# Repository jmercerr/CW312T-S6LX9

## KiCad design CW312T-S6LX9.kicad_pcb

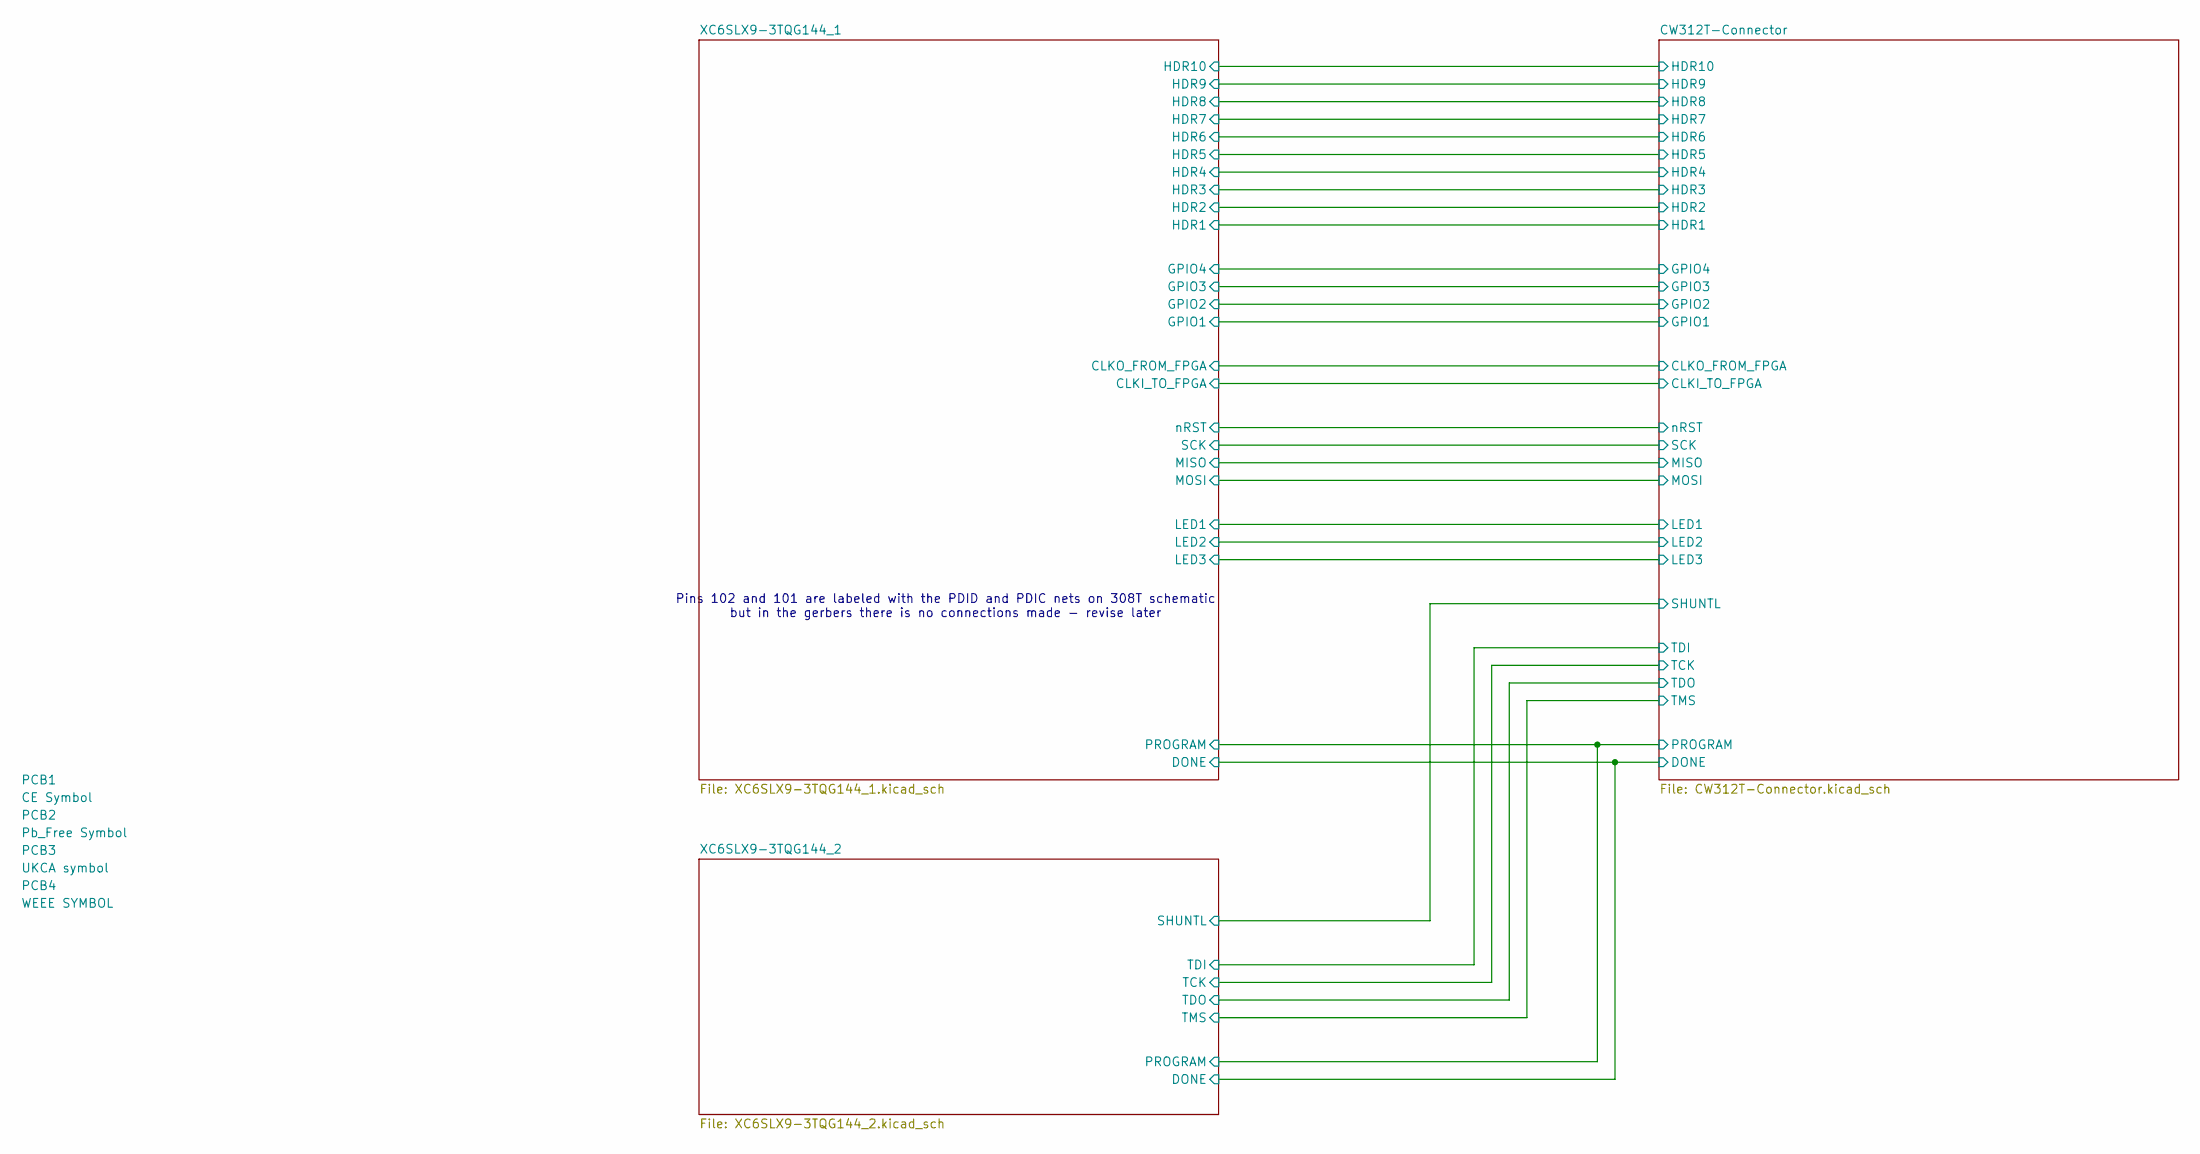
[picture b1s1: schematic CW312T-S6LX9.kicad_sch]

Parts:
PCB1: CE Symbol; CE-Logo_8.5x6mm_SilkScreen
PCB2: Pb_Free Symbol; Pb_Free_8.0x8.0mm_SilkScreen
PCB3: UKCA symbol; UKCA-Logo_8x8mm_SilkScreen
PCB4: WEEE SYMBOL; WEEE-Logo_5.6x8mm_SilkScreen

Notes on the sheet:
Pins 102 and 101 are labeled with the PDID and PDIC nets on 308T schematic but in the gerbers there is no connections made - revise later

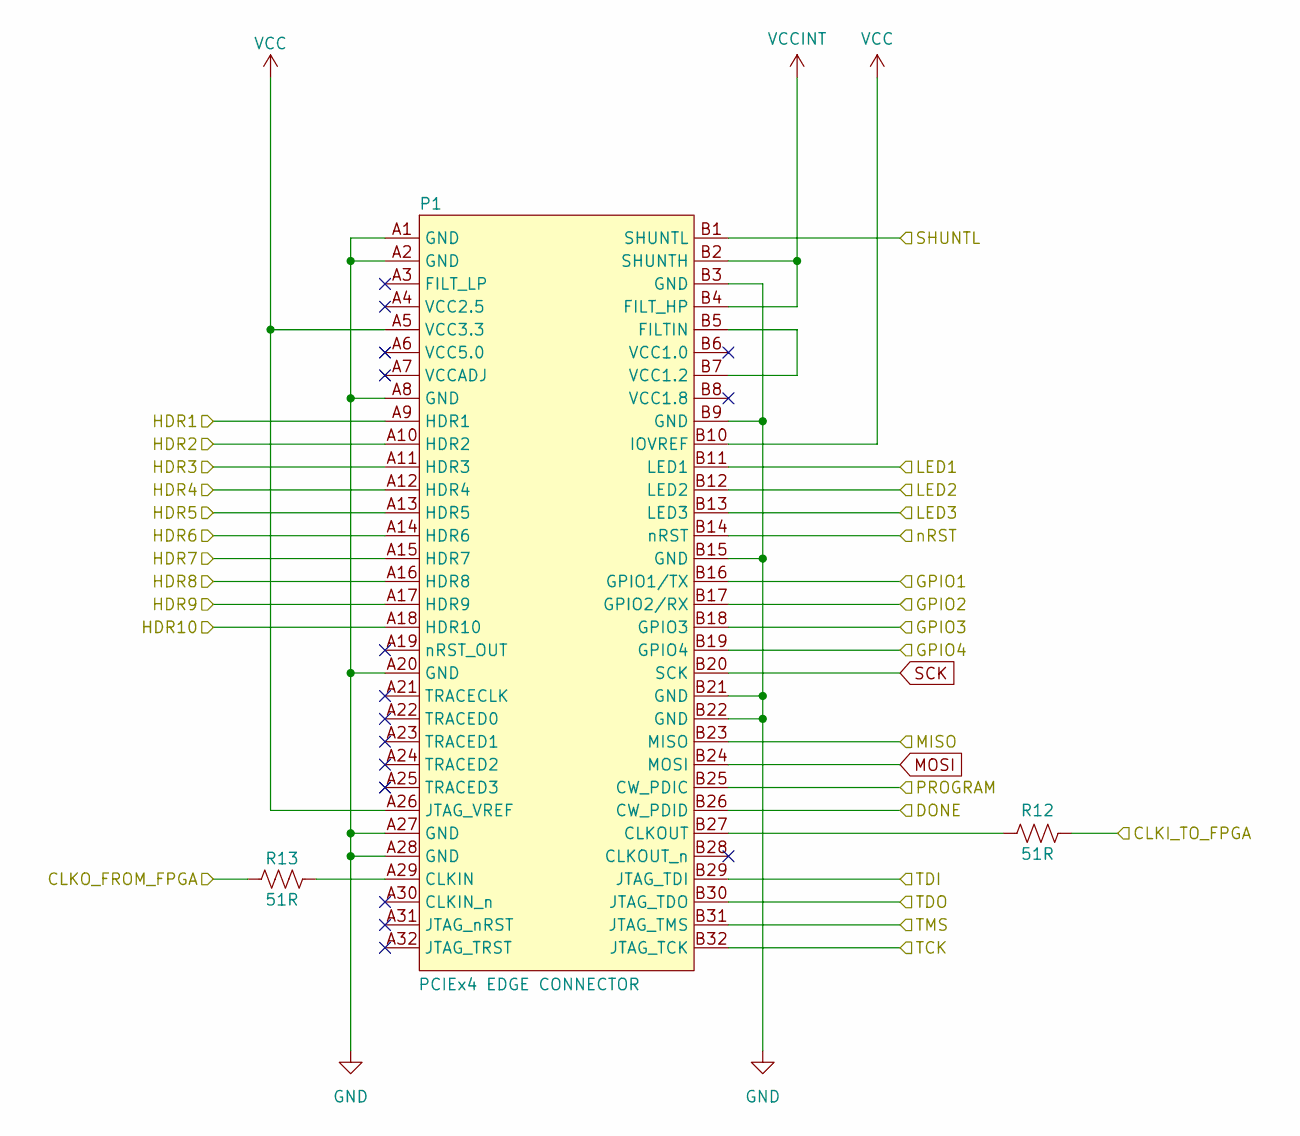
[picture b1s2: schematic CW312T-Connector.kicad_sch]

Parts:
P1: PCIEx4 EDGE CONNECTOR; CW312_Template
R12, R13: RES_51R_0603; R_0603_1608Metric; Manufacturer Part Number RC0603FR-0751RL

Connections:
/CW312T-Connector/CLKI_TO_FPGA: R12.2; also elsewhere on the board
/CW312T-Connector/CLKO_FROM_FPGA: R13.1; also elsewhere on the board
/CW312T-Connector/DONE: P1.B26 (CW_PDID); also elsewhere on the board
/CW312T-Connector/GPIO1: P1.B16 (GPIO1/TX); also elsewhere on the board
/CW312T-Connector/GPIO2: P1.B17 (GPIO2/RX); also elsewhere on the board
/CW312T-Connector/GPIO3: P1.B18 (GPIO3); also elsewhere on the board
/CW312T-Connector/GPIO4: P1.B19 (GPIO4); also elsewhere on the board
/CW312T-Connector/HDR1: P1.A9 (HDR1); also elsewhere on the board
/CW312T-Connector/HDR2: P1.A10 (HDR2); also elsewhere on the board
/CW312T-Connector/HDR3: P1.A11 (HDR3); also elsewhere on the board
/CW312T-Connector/HDR4: P1.A12 (HDR4); also elsewhere on the board
/CW312T-Connector/HDR5: P1.A13 (HDR5); also elsewhere on the board
/CW312T-Connector/HDR6: P1.A14 (HDR6); also elsewhere on the board
/CW312T-Connector/HDR7: P1.A15 (HDR7); also elsewhere on the board
/CW312T-Connector/HDR8: P1.A16 (HDR8); also elsewhere on the board
/CW312T-Connector/HDR9: P1.A17 (HDR9); also elsewhere on the board
/CW312T-Connector/HDR10: P1.A18 (HDR10); also elsewhere on the board
/CW312T-Connector/LED1: P1.B11 (LED1); also elsewhere on the board
/CW312T-Connector/LED2: P1.B12 (LED2); also elsewhere on the board
/CW312T-Connector/LED3: P1.B13 (LED3); also elsewhere on the board
/CW312T-Connector/MISO: P1.B23 (MISO); also elsewhere on the board
/CW312T-Connector/PROGRAM: P1.B25 (CW_PDIC); also elsewhere on the board
/CW312T-Connector/SHUNTL: P1.B1 (SHUNTL); also elsewhere on the board
/CW312T-Connector/TCK: P1.B32 (JTAG_TCK); also elsewhere on the board
/CW312T-Connector/TDI: P1.B29 (JTAG_TDI); also elsewhere on the board
/CW312T-Connector/TDO: P1.B30 (JTAG_TDO); also elsewhere on the board
/CW312T-Connector/TMS: P1.B31 (JTAG_TMS); also elsewhere on the board
/CW312T-Connector/nRST: P1.B14 (nRST); also elsewhere on the board
GND: P1.A1 (GND), P1.A2 (GND), P1.A8 (GND), P1.A20 (GND), P1.A27 (GND), P1.A28 (GND), P1.B3 (GND), P1.B9 (GND), P1.B15 (GND), P1.B21 (GND), P1.B22 (GND); also elsewhere on the board
MOSI: P1.B24 (MOSI); also elsewhere on the board
unnamed: P1.A29 (CLKIN), R13.2
unnamed: P1.B27 (CLKOUT), R12.1
unnamed: P1.B5 (FILTIN), P1.B7 (VCC1.2)
SCK: P1.B20 (SCK); also elsewhere on the board
VCC: P1.A5 (VCC3.3), P1.A26 (JTAG_VREF), P1.B10 (IOVREF); also elsewhere on the board
VCCINT: P1.B2 (SHUNTH), P1.B4 (FILT_HP); also elsewhere on the board

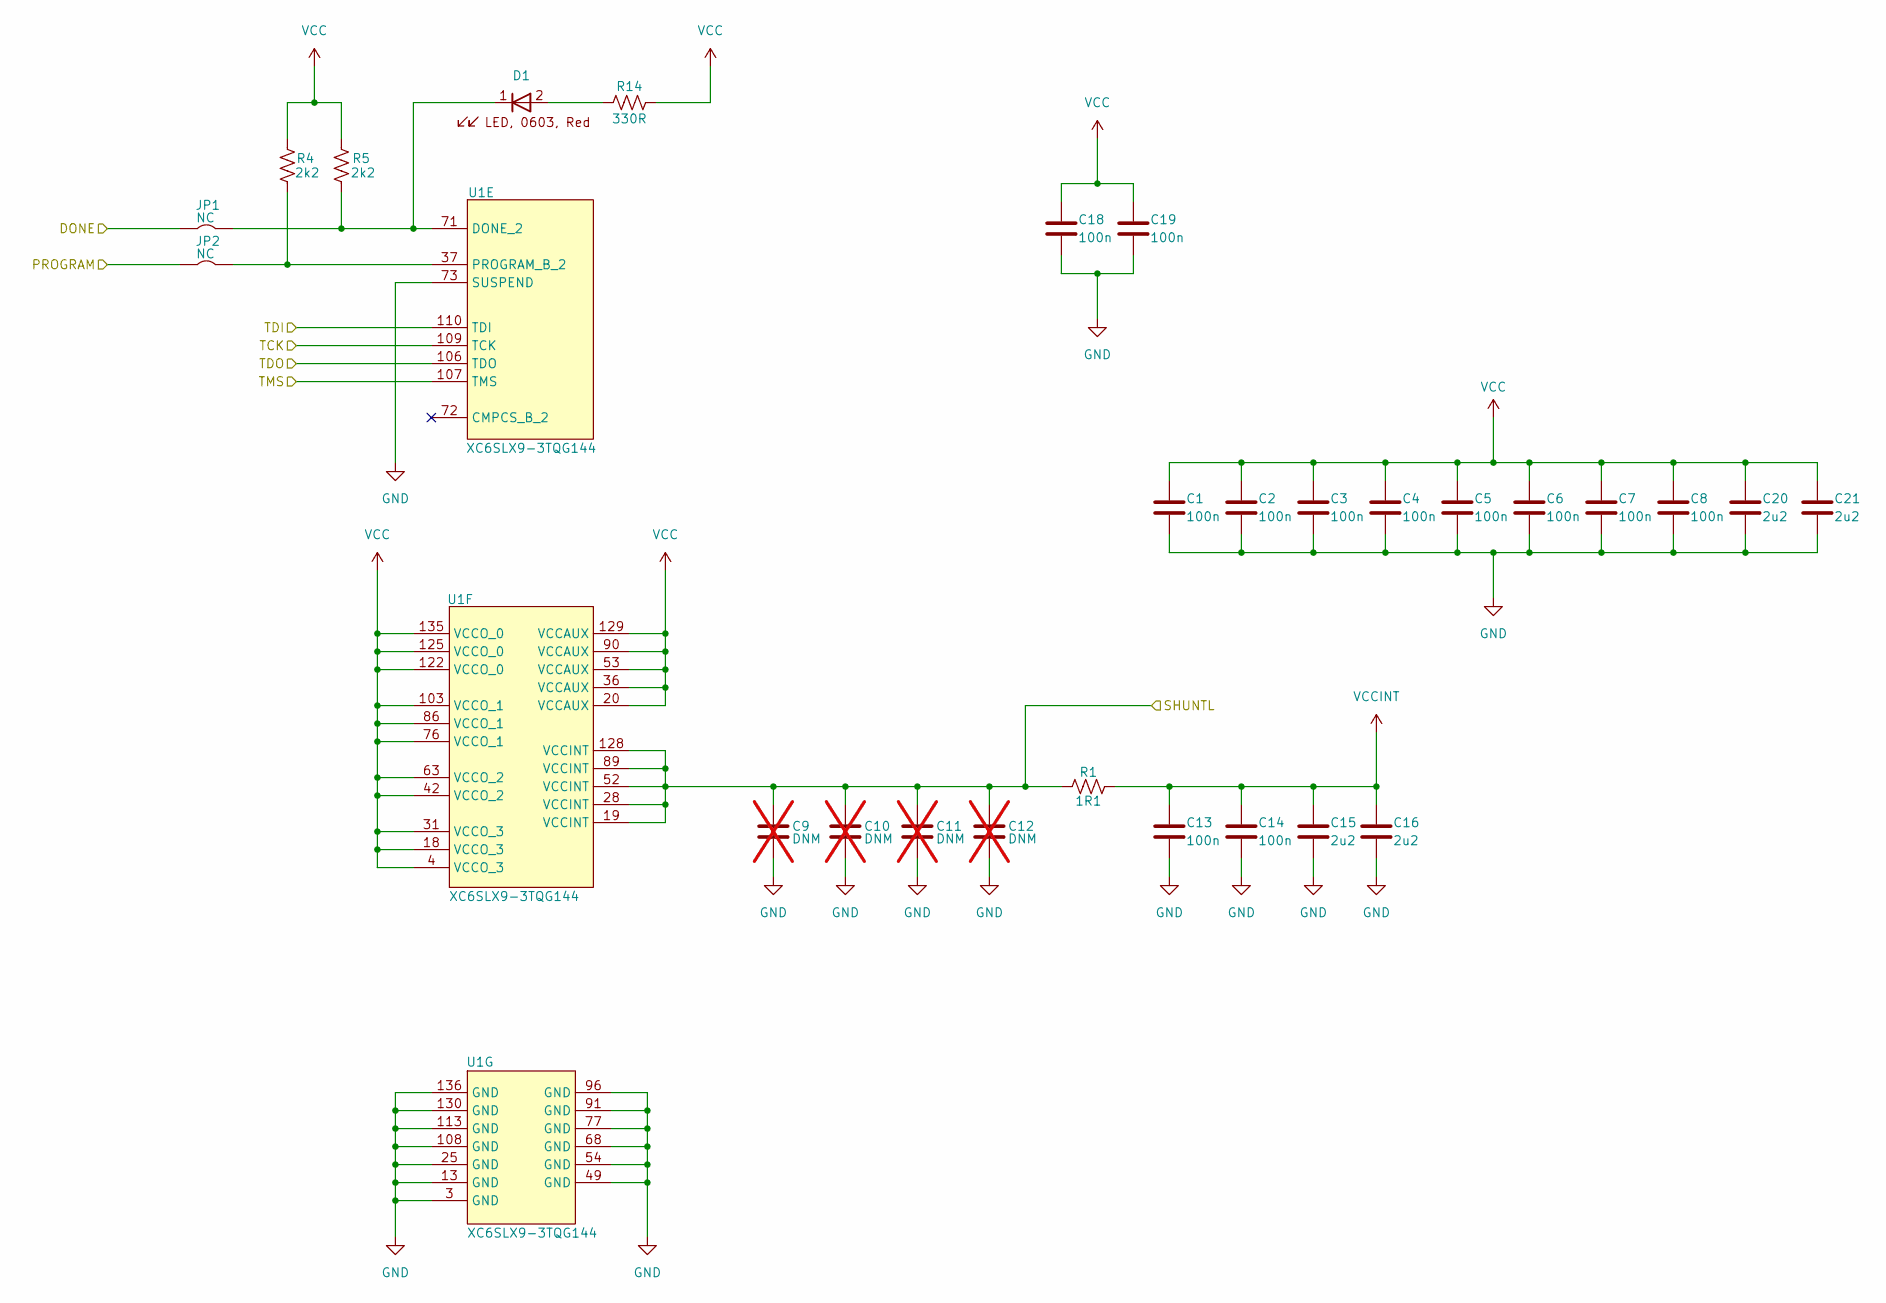
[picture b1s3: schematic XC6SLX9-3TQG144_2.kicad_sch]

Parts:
C1, C2, C3, C4, C5, C6, C7, C8, C13, C14, C18, C19: CAP_100n_6.3V_0603; C_0603_1608Metric; Manufacturer Part Number CC0603KRX7R5BB104
C9, C10, C11, C12: DNM_CAP_0603; C_0603_1608Metric; Manufacturer Part Number C0603C225K4PAC7867; not fitted
C15, C16, C20, C21: CAP_2u2_6.3V_0603; C_0603_1608Metric; Manufacturer Part Number CC0603KRX7R5BB225
D1: APT1608SRCPRV; LED_0603_1608Metric; Manufacturer Part Number APT1608SRCPRV
JP1, JP2: SolderJumper-2_P1.3mm_Bridged2Bar_Pad1.0x1.5mm
R1: RES_1R1_0603; R_0603_1608Metric; Manufacturer Part Number RC0603FR-101R1L
R4, R5: RES_2k2_0603; R_0603_1608Metric; Manufacturer Part Number RC0603FR-072K2L
R14: RES_330R_0603; R_0603_1608Metric; Manufacturer Part Number RC0603FR-07330RL
U1: XC6SLX9-3TQG144; TQFP-144_20x20mm_P0.5mm; Manufacturer Part Number XC6SLX9-3TQG144CXC6SLX9-3TQG144C

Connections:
/CW312T-Connector/DONE: JP1.1; also elsewhere on the board
/CW312T-Connector/PROGRAM: JP2.1; also elsewhere on the board
/CW312T-Connector/SHUNTL: C9.2, C10.2, C11.2, C12.2, R1.1, U1.19 (VCCINT), U1.28 (VCCINT), U1.52 (VCCINT), U1.89 (VCCINT), U1.128 (VCCINT); also elsewhere on the board
/CW312T-Connector/TCK: U1.109 (TCK); also elsewhere on the board
/CW312T-Connector/TDI: U1.110 (TDI); also elsewhere on the board
/CW312T-Connector/TDO: U1.106 (TDO); also elsewhere on the board
/CW312T-Connector/TMS: U1.107 (TMS); also elsewhere on the board
GND: C1.2, C2.2, C3.2, C4.2, C5.2, C6.2, C7.2, C8.2, C9.1, C10.1, C11.1, C12.1, C13.2, C14.2, C15.2, C16.2, C18.2, C19.2, C20.2, C21.2, U1.3 (GND), U1.13 (GND), U1.25 (GND), U1.49 (GND), U1.54 (GND), U1.68 (GND), U1.73 (SUSPEND), U1.77 (GND), U1.91 (GND), U1.96 (GND), U1.108 (GND), U1.113 (GND), U1.130 (GND), U1.136 (GND); also elsewhere on the board
unnamed: D1.2, R14.1
unnamed: D1.1, JP1.2, R5.1, U1.71 (DONE_2)
unnamed: JP2.2, R4.1, U1.37 (PROGRAM_B_2)
VCC: C1.1, C2.1, C3.1, C4.1, C5.1, C6.1, C7.1, C8.1, C18.1, C19.1, C20.1, C21.1, R4.2, R5.2, R14.2, U1.4 (VCCO_3), U1.18 (VCCO_3), U1.20 (VCCAUX), U1.31 (VCCO_3), U1.36 (VCCAUX), U1.42 (VCCO_2), U1.53 (VCCAUX), U1.63 (VCCO_2), U1.76 (VCCO_1), U1.86 (VCCO_1), U1.90 (VCCAUX), U1.103 (VCCO_1), U1.122 (VCCO_0), U1.125 (VCCO_0), U1.129 (VCCAUX), U1.135 (VCCO_0); also elsewhere on the board
VCCINT: C13.1, C14.1, C15.1, C16.1, R1.2; also elsewhere on the board

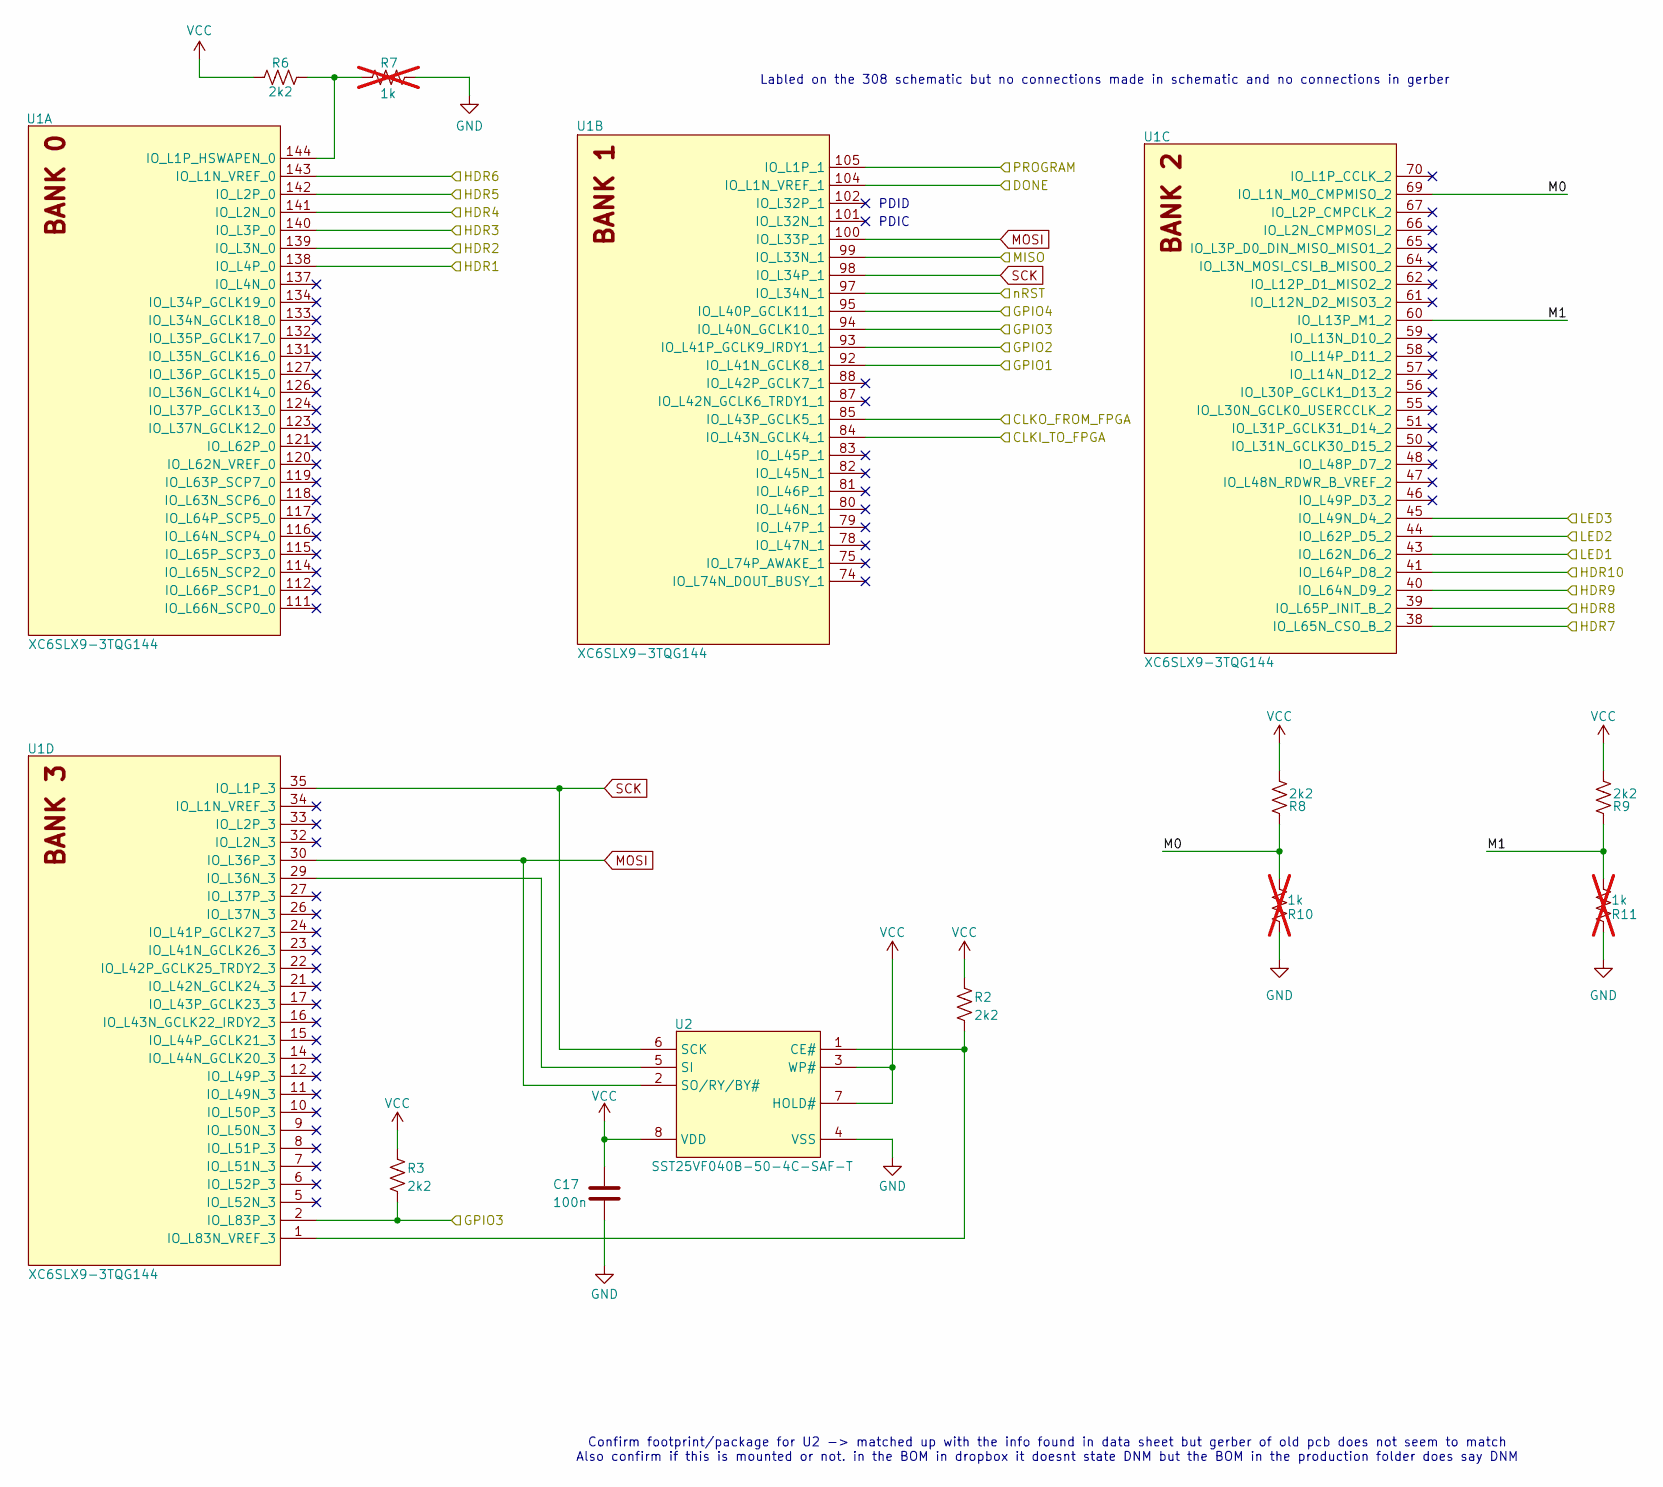
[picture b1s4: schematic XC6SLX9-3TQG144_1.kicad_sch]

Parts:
C17: CAP_100n_6.3V_0603; C_0603_1608Metric; Manufacturer Part Number CC0603KRX7R5BB104
R2, R3, R6, R8, R9: RES_2k2_0603; R_0603_1608Metric; Manufacturer Part Number RC0603FR-072K2L
R7, R10, R11: RES_1k_0603; R_0603_1608Metric; Manufacturer Part Number RC0603FR-071KL; not fitted
U1: XC6SLX9-3TQG144; TQFP-144_20x20mm_P0.5mm; Manufacturer Part Number XC6SLX9-3TQG144CXC6SLX9-3TQG144C
U2: SST25VF040B-50-4C-SAF-T; SOIC-8_5.275x5.275mm_P1.27mm; Manufacturer Part Number SST25VF040B-50-4C-SAF-T

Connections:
/CW312T-Connector/CLKI_TO_FPGA: U1.84 (IO_L43N_GCLK4_1); also elsewhere on the board
/CW312T-Connector/CLKO_FROM_FPGA: U1.85 (IO_L43P_GCLK5_1); also elsewhere on the board
/CW312T-Connector/DONE: U1.104 (IO_L1N_VREF_1); also elsewhere on the board
/CW312T-Connector/GPIO1: U1.92 (IO_L41N_GCLK8_1); also elsewhere on the board
/CW312T-Connector/GPIO2: U1.93 (IO_L41P_GCLK9_IRDY1_1); also elsewhere on the board
/CW312T-Connector/GPIO3: R3.1, U1.2 (IO_L83P_3), U1.94 (IO_L40N_GCLK10_1); also elsewhere on the board
/CW312T-Connector/GPIO4: U1.95 (IO_L40P_GCLK11_1); also elsewhere on the board
/CW312T-Connector/HDR1: U1.138 (IO_L4P_0); also elsewhere on the board
/CW312T-Connector/HDR2: U1.139 (IO_L3N_0); also elsewhere on the board
/CW312T-Connector/HDR3: U1.140 (IO_L3P_0); also elsewhere on the board
/CW312T-Connector/HDR4: U1.141 (IO_L2N_0); also elsewhere on the board
/CW312T-Connector/HDR5: U1.142 (IO_L2P_0); also elsewhere on the board
/CW312T-Connector/HDR6: U1.143 (IO_L1N_VREF_0); also elsewhere on the board
/CW312T-Connector/HDR7: U1.38 (IO_L65N_CSO_B_2); also elsewhere on the board
/CW312T-Connector/HDR8: U1.39 (IO_L65P_INIT_B_2); also elsewhere on the board
/CW312T-Connector/HDR9: U1.40 (IO_L64N_D9_2); also elsewhere on the board
/CW312T-Connector/HDR10: U1.41 (IO_L64P_D8_2); also elsewhere on the board
/CW312T-Connector/LED1: U1.43 (IO_L62N_D6_2); also elsewhere on the board
/CW312T-Connector/LED2: U1.44 (IO_L62P_D5_2); also elsewhere on the board
/CW312T-Connector/LED3: U1.45 (IO_L49N_D4_2); also elsewhere on the board
/CW312T-Connector/MISO: U1.99 (IO_L33N_1); also elsewhere on the board
/CW312T-Connector/PROGRAM: U1.105 (IO_L1P_1); also elsewhere on the board
/CW312T-Connector/nRST: U1.97 (IO_L34N_1); also elsewhere on the board
/XC6SLX9-3TQG144_1/M0: R8.1, R10.2, U1.69 (IO_L1N_M0_CMPMISO_2)
/XC6SLX9-3TQG144_1/M1: R9.1, R11.2, U1.60 (IO_L13P_M1_2)
GND: C17.2, R7.1, R10.1, R11.1, U2.4 (VSS); also elsewhere on the board
MOSI: U1.30 (IO_L36P_3), U1.100 (IO_L33P_1), U2.2 (SO/RY/BY#); also elsewhere on the board
unnamed: R6.2, R7.2, U1.144 (IO_L1P_HSWAPEN_0)
unnamed: U1.29 (IO_L36N_3), U2.5 (SI)
unnamed: R2.1, U1.1 (IO_L83N_VREF_3), U2.1 (CE#)
SCK: U1.35 (IO_L1P_3), U1.98 (IO_L34P_1), U2.6 (SCK); also elsewhere on the board
VCC: C17.1, R2.2, R3.2, R6.1, R8.2, R9.2, U2.3 (WP#), U2.7 (HOLD#), U2.8 (VDD); also elsewhere on the board

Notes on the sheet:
PDID
Labled on the 308 schematic but no connections made in schematic and no connections in gerber
PDIC
Confirm footprint/package for U2 -> matched up with the info found in data sheet but gerber of old pcb does not seem to match Also confirm if this is mounted or not. in the BOM in dropbox it doesnt state DNM but the BOM in the production folder does say DNM

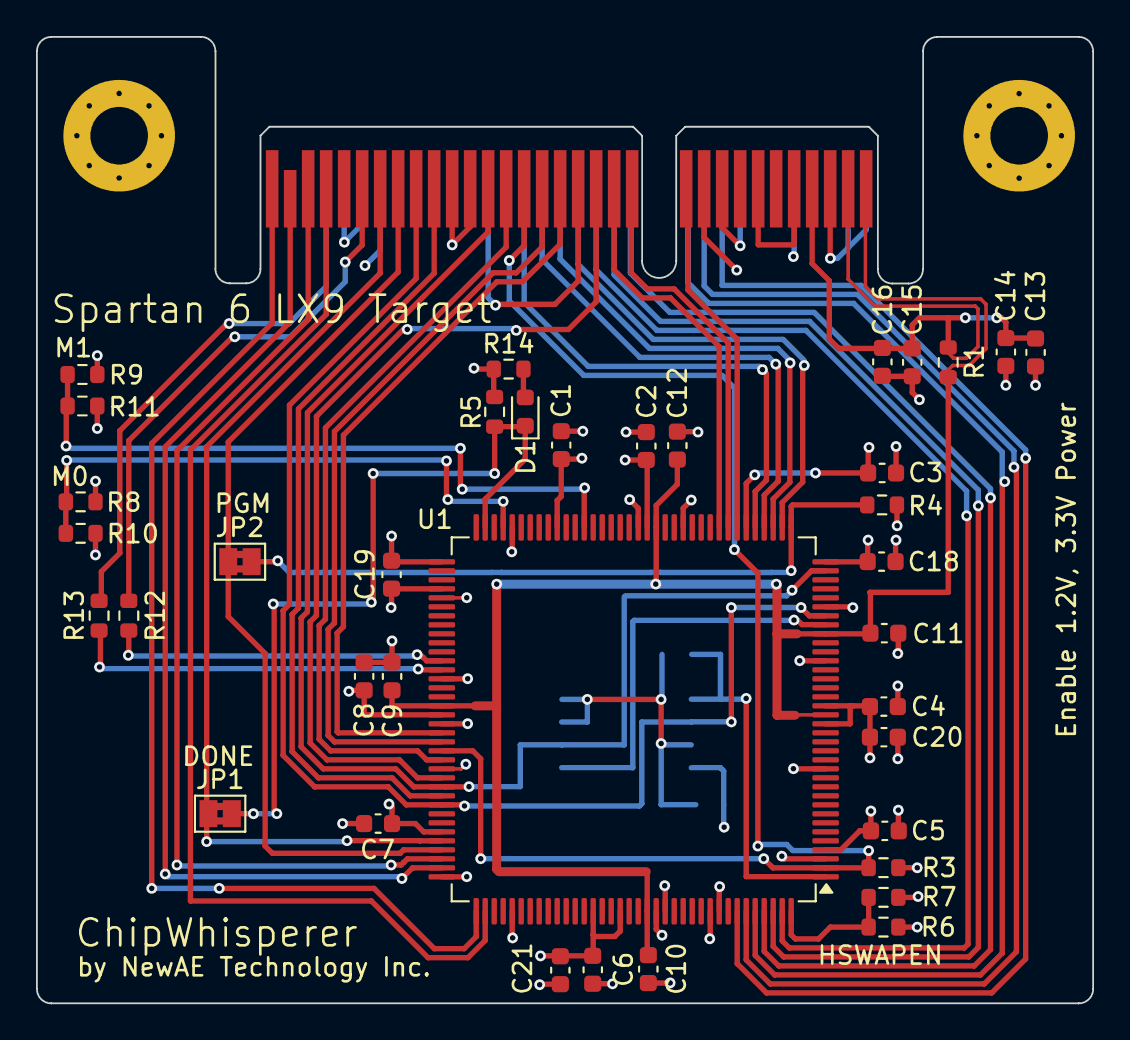
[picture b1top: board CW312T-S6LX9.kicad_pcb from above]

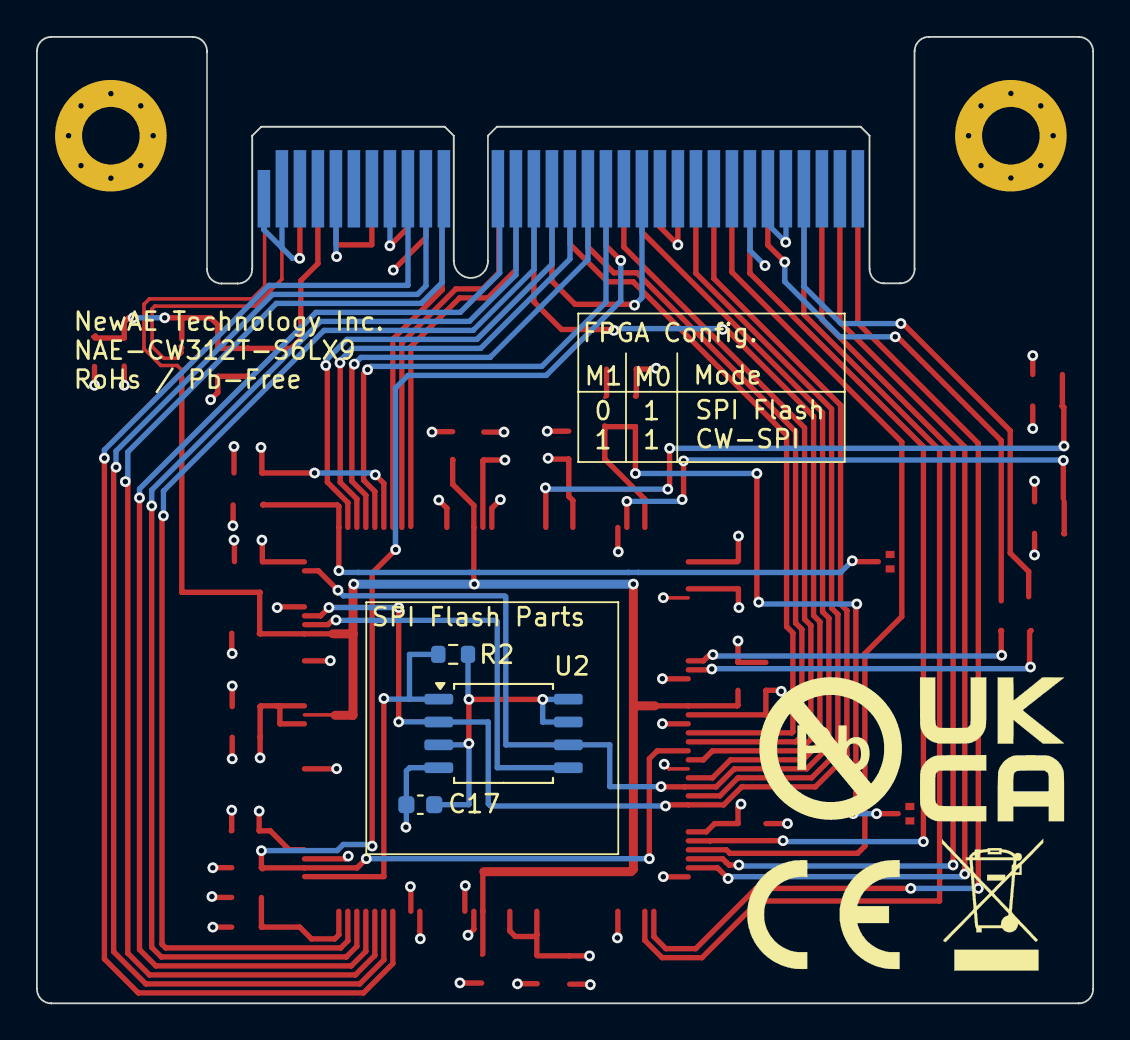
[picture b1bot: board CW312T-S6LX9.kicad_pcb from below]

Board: 4 copper layers, 58.7 x 53.7 mm, 45 parts (3 on the bottom side), 44 nets.

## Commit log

2024-11-21 updated design - still needs vcc routing
2024-11-22 updated cw312t template
2024-11-22 added inner layers for gnd and pwr planes, added silkscreen, updated cw312t template
2024-11-26 first draft - ready for review
2024-12-03 updated schematic and pcb, fixed silkscreen - Ready for review
2024-12-03 updated note on schematic
2024-12-19 updated schematic and pcb after library re-organization
2024-12-19 updated pcb and schematic after library re-organization
